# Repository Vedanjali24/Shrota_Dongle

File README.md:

# Shrota_Dongle
The Shrota Dongle is a custom-designed Ground Control Station (GCS) telemetry interface PCB developed as part of our rocketry team’s avionics and communication system. The board enables reliable reception and processing of real-time telemetry transmitted from the rocket during flight.

The system is built around an STM32 microcontroller, which manages telemetry data handling and communication with a LoRa RYLR module used for long-range wireless data reception. This allows the ground station to receive critical flight parameters and system status during launch and testing.

The PCB features a 5.5 V to 3.3 V regulated power architecture with VCC filtering to ensure stable operation of RF and digital components. High-speed and low-speed oscillators provide precise timing, while external SPI Flash memory allows telemetry data to be logged for redundancy and post-flight analysis.

Developed collaboratively as part of our team’s ground infrastructure, the Shrota Dongle provides a robust communication link for monitoring mission-critical rocket performance.

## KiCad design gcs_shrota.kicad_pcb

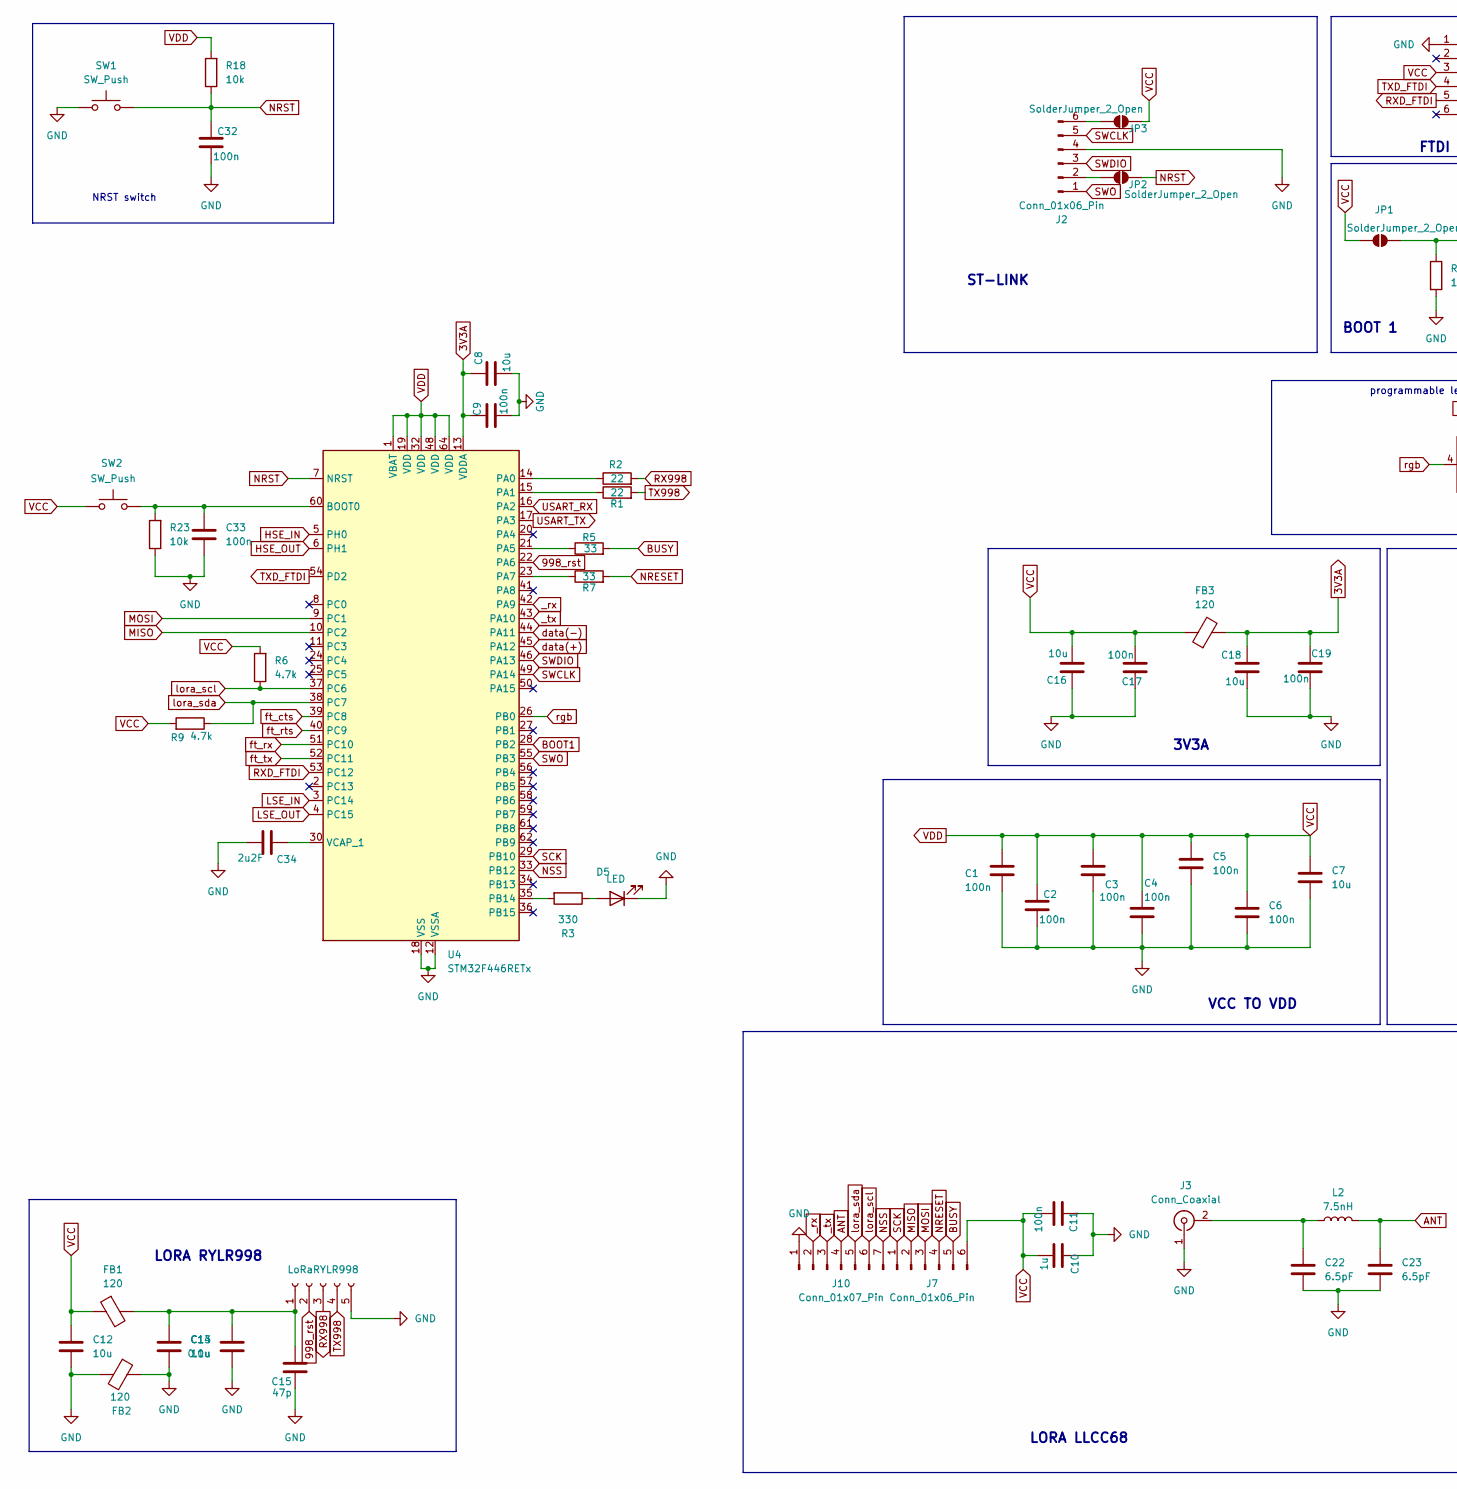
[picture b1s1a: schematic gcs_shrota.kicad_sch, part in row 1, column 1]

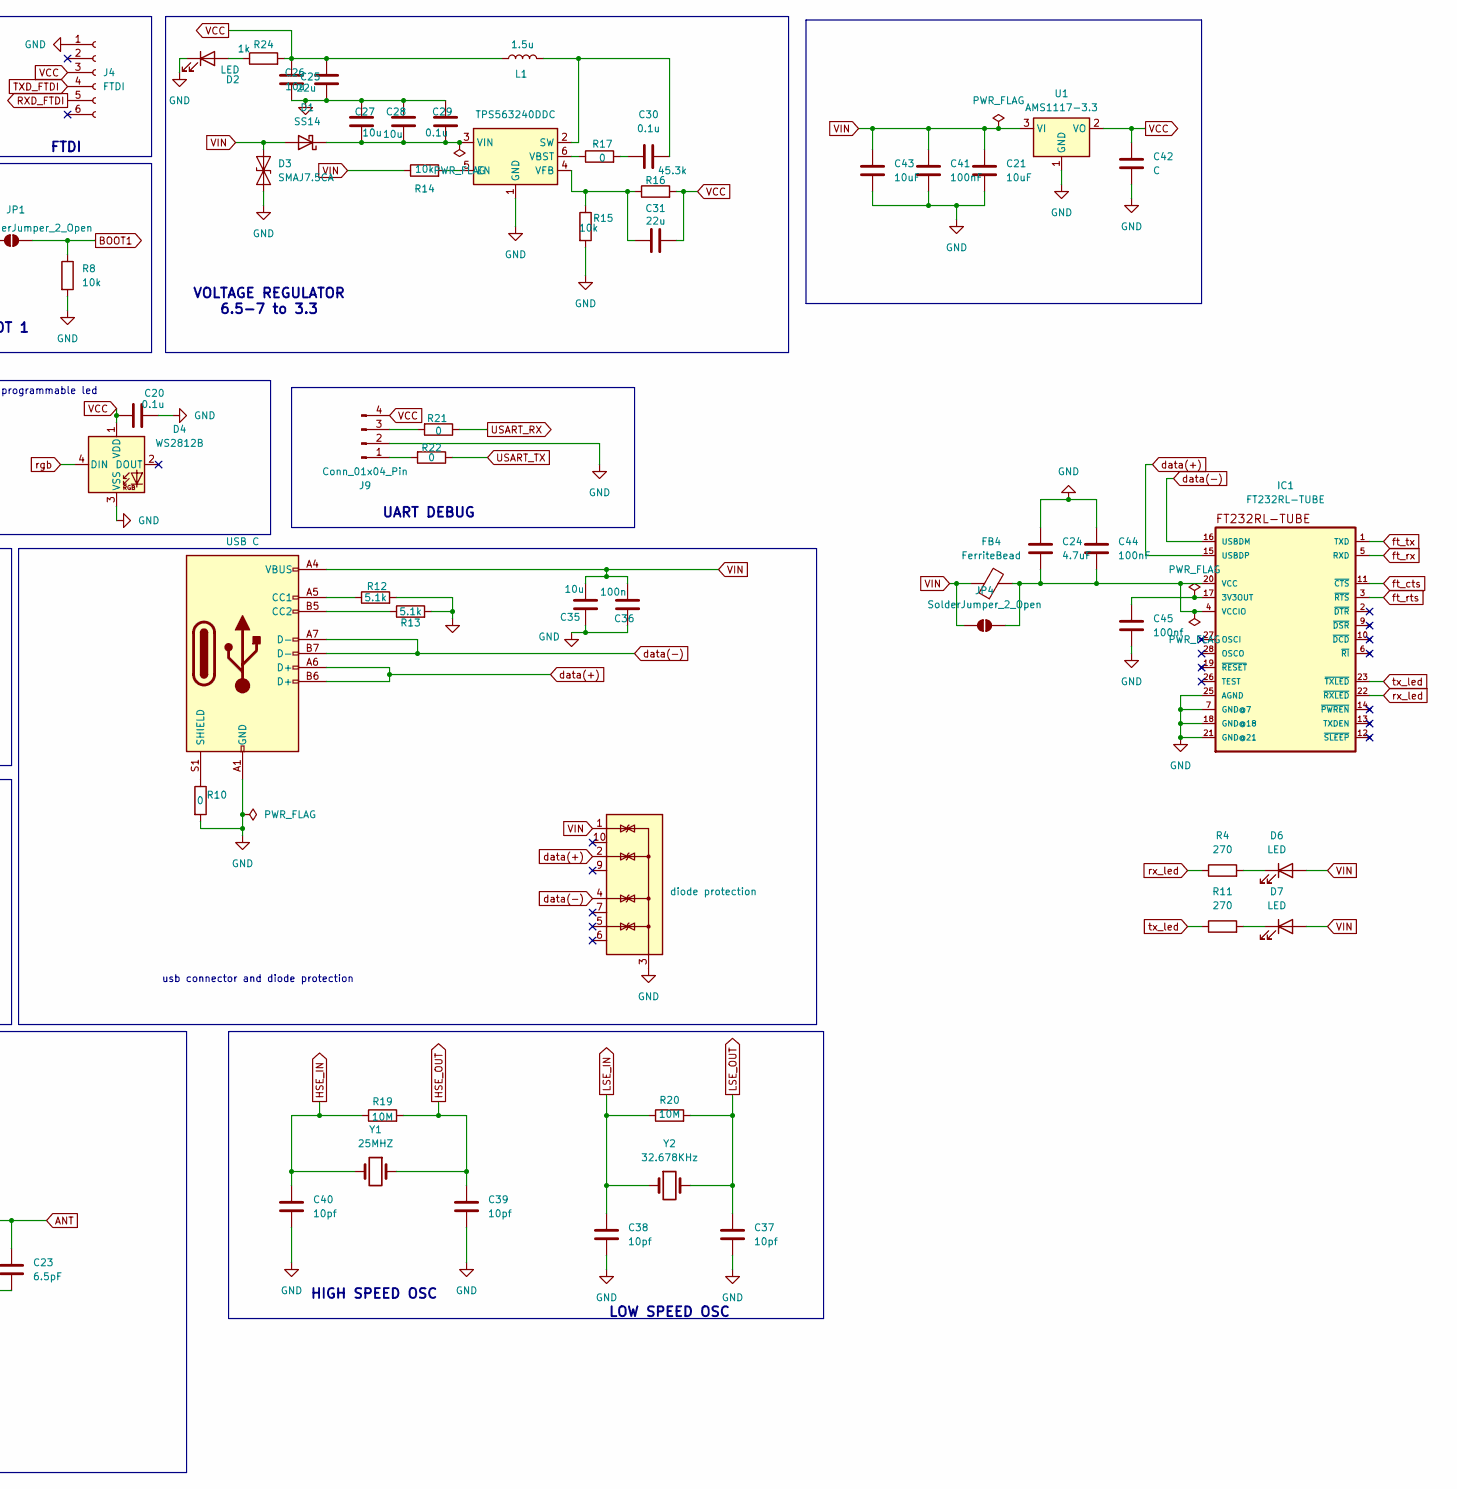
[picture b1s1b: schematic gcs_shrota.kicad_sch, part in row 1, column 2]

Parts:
C1, C2, C3, C4, C5, C6, C9, C11, C17, C19, C32, C33, C36: 100n; C_0603_1608Metric_Pad1.08x0.95mm_HandSolder
C7, C8, C12, C13, C16, C18, C26, C27, C28, C35: 10u; C_0603_1608Metric_Pad1.08x0.95mm_HandSolder
C10: 1u; C_0603_1608Metric_Pad1.08x0.95mm_HandSolder
C14, C20, C29, C30: 0.1u; C_0603_1608Metric_Pad1.08x0.95mm_HandSolder
C15: 47p; C_0603_1608Metric_Pad1.08x0.95mm_HandSolder
C21, C43: 10uF; C_0603_1608Metric_Pad1.08x0.95mm_HandSolder
C22, C23: 6.5pF; C_0603_1608Metric_Pad1.08x0.95mm_HandSolder
C24: 4.7uF; C_0603_1608Metric_Pad1.08x0.95mm_HandSolder
C25, C31: 22u; C_0603_1608Metric_Pad1.08x0.95mm_HandSolder
C34: 2u2F; C_0603_1608Metric_Pad1.08x0.95mm_HandSolder
C37, C38, C39, C40: 10pf; C_0603_1608Metric_Pad1.08x0.95mm_HandSolder
C41, C44: 100nF; C_0603_1608Metric_Pad1.08x0.95mm_HandSolder
C42: C; C_0603_1608Metric_Pad1.08x0.95mm_HandSolder
C45: 100nf; C_0603_1608Metric_Pad1.08x0.95mm_HandSolder
D1: SS14; D_SMA_Handsoldering
D2: LED; LED_0603_1608Metric_Pad1.05x0.95mm_HandSolder
D3: SMAJ7.5CA; D_SMA_Handsoldering
D4: WS2812B; LED_WS2812B_PLCC4_5.0x5.0mm_P3.2mm
D5: LED; D_0603_1608Metric_Pad1.05x0.95mm_HandSolder
D6, D7: LED; C_0603_1608Metric_Pad1.08x0.95mm_HandSolder
FB1, FB2, FB3: 120; L_0603_1608Metric_Pad1.05x0.95mm_HandSolder
FB4: FerriteBead; L_0603_1608Metric_Pad1.05x0.95mm_HandSolder
IC1: FT232RL-TUBE; SSOP28-LD
J1: LoRaRYLR998; PinSocket_1x05_P2.54mm_Vertical
J2, J7: Conn_01x06_Pin; PinHeader_1x06_P2.54mm_Vertical
J3: Conn_Coaxial; SMA_Amphenol_901-144_Vertical
J4: FTDI; PinSocket_1x06_P2.54mm_Vertical
J5: USB C; USB_C_Receptacle_GCT_USB4105-xx-A_16P_TopMnt_Horizontal
J9: Conn_01x04_Pin; PinSocket_1x04_P2.54mm_Vertical
J10: Conn_01x07_Pin; PinHeader_1x07_P2.54mm_Vertical
JP1, JP2, JP3, JP4: SolderJumper_2_Open; SolderJumper-2_P1.3mm_Open_Pad1.0x1.5mm
L1: 1.5u; L_Sunlord_SWPA3015S
L2: 7.5nH; L_0603_1608Metric_Pad1.05x0.95mm_HandSolder
R1, R2: 22; R_0603_1608Metric_Pad0.98x0.95mm_HandSolder
R3: 330; D_0603_1608Metric_Pad1.05x0.95mm_HandSolder
R4, R11: 270; R_0603_1608Metric_Pad0.98x0.95mm_HandSolder
R5, R7: 33; R_0603_1608Metric_Pad0.98x0.95mm_HandSolder
R6, R9: 4.7k; R_0603_1608Metric_Pad0.98x0.95mm_HandSolder
R8, R14, R15, R18, R23: 10k; R_0603_1608Metric_Pad0.98x0.95mm_HandSolder
R10, R17, R21, R22: 0; R_0603_1608Metric_Pad0.98x0.95mm_HandSolder
R12, R13: 5.1k; R_0603_1608Metric_Pad0.98x0.95mm_HandSolder
R16: 45.3k; R_0603_1608Metric_Pad0.98x0.95mm_HandSolder
R19, R20: 10M; R_0603_1608Metric_Pad0.98x0.95mm_HandSolder
R24: 1k; R_0603_1608Metric_Pad0.98x0.95mm_HandSolder
SW1, SW2: SW_Push; SW_PUSH_6mm
U1: AMS1117-3.3; SOT-223-3_TabPin2
U2: diode protection; USON-10_2.5x1.0mm_P0.5mm
U3: TPS563240DDC; SOT-23-6_Handsoldering
U4: STM32F446RETx; LQFP-64_10x10mm_P0.5mm
Y1: 25MHZ; XTAL_ABLS-25.000MHZ-B2F-T
Y2: 32.678KHz; Crystal_SMD_0603-2Pin_6.0x3.5mm

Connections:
3V3A: C8.1, C9.2, C18.1, C19.2, FB3.2, U4.13 (VDDA)
998_rst: J1.2, U4.22 (PA6)
ANT: C23.1, J10.4, L2.2
BOOT1: JP1.2 (B), R8.1, U4.28 (PB2)
BUSY: J7.5, R5.2
GND: C1.2, C2.2, C3.2, C4.2, C5.2, C6.2, C7.2, C8.2, C9.1, C10.2, C11.2, C12.2, C13.2, C14.2, C15.2, C16.1, C17.2, C18.2, C19.1, C20.2, C21.2, C22.2, C23.2, C24.1, C25.2, C26.2, C27.1, C28.1, C29.1, C32.2, C33.2, C34.1, C35.1, C36.2, C37.2, C38.2, C39.2, C40.2, C41.2, C42.2, C43.2, C44.1, C45.2, D2.1 (K), D3.1 (A1), D4.3 (VSS), D5.1 (K), FB2.1, FB2.2, IC1.7 (GND@7), IC1.18 (GND@18), IC1.21 (GND@21), IC1.25 (AGND), J1.5, J2.4, J3.1 (In), J4.1, J5.A1 (GND), J5.A12 (GND), J5.B1 (GND), J5.B12 (GND), J9.2, J10.1, R8.2, R10.2, R12.2, R13.2, R15.2, R23.1, SW1.1, U1.1 (GND), U2.3 (G), U2.8 (G), U3.1 (GND), U4.12 (VSSA), U4.18 (VSS), U4.31 (VSS), U4.47 (VSS), U4.63 (VSS)
HSE_IN: C40.1, R19.1, U4.5 (PH0), Y1.2
HSE_OUT: C39.1, R19.2, U4.6 (PH1), Y1.1
LSE_IN: C38.1, R20.1, U4.3 (PC14), Y2.1
LSE_OUT: C37.1, R20.2, U4.4 (PC15), Y2.2
MISO: J7.2, U4.10 (PC2)
MOSI: J7.3, U4.9 (PC1)
NRESET: J7.4, R7.2
NSS: J10.7, U4.33 (PB12)
unnamed: C30.1, R17.2
unnamed: C27.2, C28.2, C29.2, D1.1 (K), U3.3 (VIN)
unnamed: D2.2 (A), R24.1
unnamed: D5.2 (A), R3.1
unnamed: D6.1 (K), R4.2
unnamed: D7.1 (K), R11.2
unnamed: C45.1, IC1.17 (3V3OUT)
unnamed: C24.2, C44.2, FB4.2, IC1.4 (VCCIO), IC1.20 (VCC), JP4.2 (B)
unnamed: C13.1, C14.1, C15.1, FB1.2, J1.1
unnamed: J2.6, JP3.1 (A)
unnamed: C22.1, J3.2 (Ext), L2.1
unnamed: J5.A5 (CC1), R12.1
unnamed: J5.B5 (CC2), R13.1
unnamed: J5.S1 (SHIELD), R10.1
unnamed: J9.1, R22.2
unnamed: J9.3, R21.2
unnamed: R14.2, U3.5 (EN)
unnamed: C30.2, L1.2, U3.2 (SW)
unnamed: R17.1, U3.6 (VBST)
unnamed: C31.1, R15.1, R16.1, U3.4 (VFB)
unnamed: C33.1, R23.2, SW2.1, U4.60 (BOOT0)
unnamed: R2.1, U4.14 (PA0)
unnamed: R1.1, U4.15 (PA1)
unnamed: R5.1, U4.21 (PA5)
unnamed: R7.1, U4.23 (PA7)
unnamed: R3.2, U4.35 (PB14)
unnamed: C34.2, U4.30 (VCAP_1)
RX998: J1.3, R2.2
RXD_FTDI: J4.5, U4.53 (PC12)
SCK: J7.1, U4.29 (PB10)
SWCLK: J2.5, U4.49 (PA14)
SWDIO: J2.3, U4.46 (PA13)
SWO: J2.1, U4.55 (PB3)
TX998: J1.4, R1.2
TXD_FTDI: J4.4, U4.54 (PD2)
USART_RX: R21.1, U4.16 (PA2)
USART_TX: R22.1, U4.17 (PA3)
VCC: C1.1, C2.1, C3.1, C4.1, C5.1, C6.1, C7.1, C10.1, C11.1, C12.1, C16.2, C17.1, C20.1, C25.1, C26.1, C31.2, C42.1, D4.1 (VDD), FB1.1, FB3.1, J4.3, J7.6, J9.4, JP1.1 (A), JP3.2 (B), L1.1, R6.2, R9.2, R16.2, R18.2, R24.2, SW2.2, U1.2 (VO), U4.1 (VBAT), U4.19 (VDD), U4.32 (VDD), U4.48 (VDD), U4.64 (VDD)
VIN: C21.1, C35.2, C36.1, C41.1, C43.1, D1.2 (A), D3.2 (A2), D6.2 (A), D7.2 (A), FB4.1, J5.A4 (VBUS), J5.A9 (VBUS), J5.B4 (VBUS), J5.B9 (VBUS), JP4.1 (A), R14.1, U1.3 (VI), U2.1 (IO1)
_rx: J10.2, U4.42 (PA9)
_tx: J10.3, U4.43 (PA10)
data(+): IC1.15 (USBDP), J5.A6 (D+), J5.B6 (D+), U2.2 (IO2), U4.45 (PA12)
data(-): IC1.16 (USBDM), J5.A7 (D-), J5.B7 (D-), U2.4 (IO3), U4.44 (PA11)
ft_cts: IC1.11 (~CTS), U4.39 (PC8)
ft_rts: IC1.3 (~RTS), U4.40 (PC9)
ft_rx: IC1.5 (RXD), U4.51 (PC10)
ft_tx: IC1.1 (TXD), U4.52 (PC11)
lora_scl: J10.6, R6.1, U4.37 (PC6)
lora_sda: J10.5, R9.1, U4.38 (PC7)
rgb: D4.4 (DIN), U4.26 (PB0)
rx_led: IC1.22 (~RXLED), R4.1
tx_led: IC1.23 (~TXLED), R11.1

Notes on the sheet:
BOOT 1
VOLTAGE REGULATOR 6.5-7 to 3.3
LORA LLCC68
LOW SPEED OSC
VCC TO VDD
LORA RYLR998
3V3A
NRST switch
FTDI
programmable led
ST-LINK
UART DEBUG
usb connector and diode protection
HIGH SPEED OSC

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
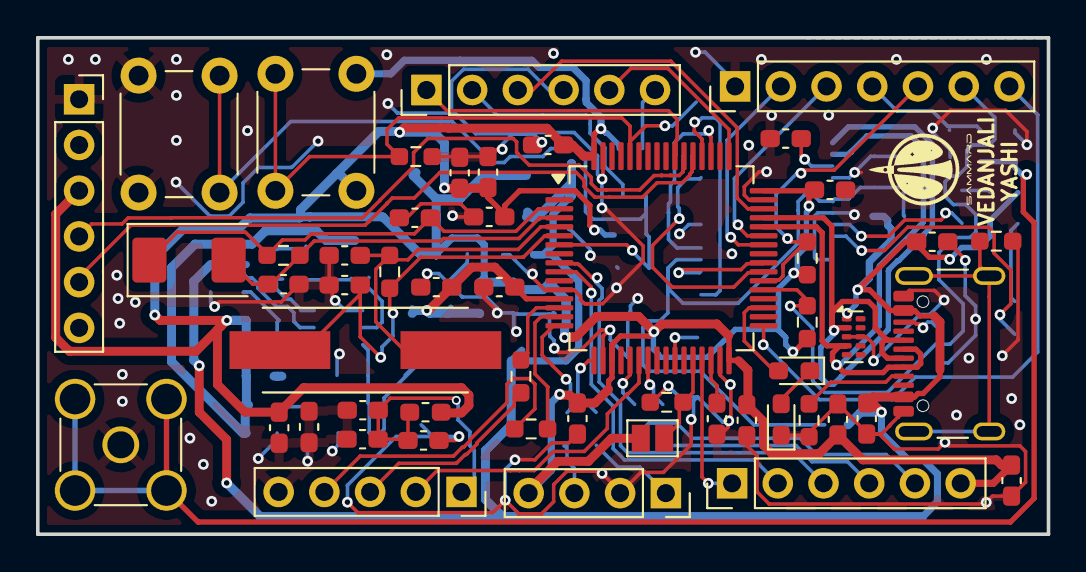
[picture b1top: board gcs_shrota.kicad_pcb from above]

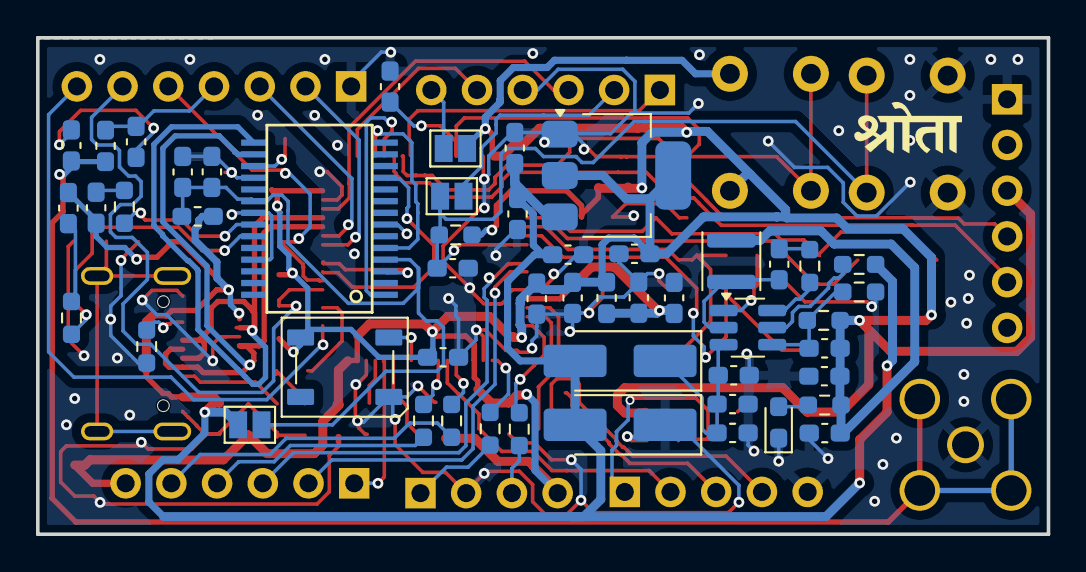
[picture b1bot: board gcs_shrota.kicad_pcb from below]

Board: 2 copper layers, 56.1 x 27.6 mm, 103 parts (51 on the bottom side), 68 nets.

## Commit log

2026-03-10 Enhance README with detailed Shrota Dongle description
    Expanded the description of the Shrota Dongle to provide detailed information about its functionality, components, and collaborative development.
2026-03-10 Add images to README for better visualization
    Added images to enhance the documentation.
